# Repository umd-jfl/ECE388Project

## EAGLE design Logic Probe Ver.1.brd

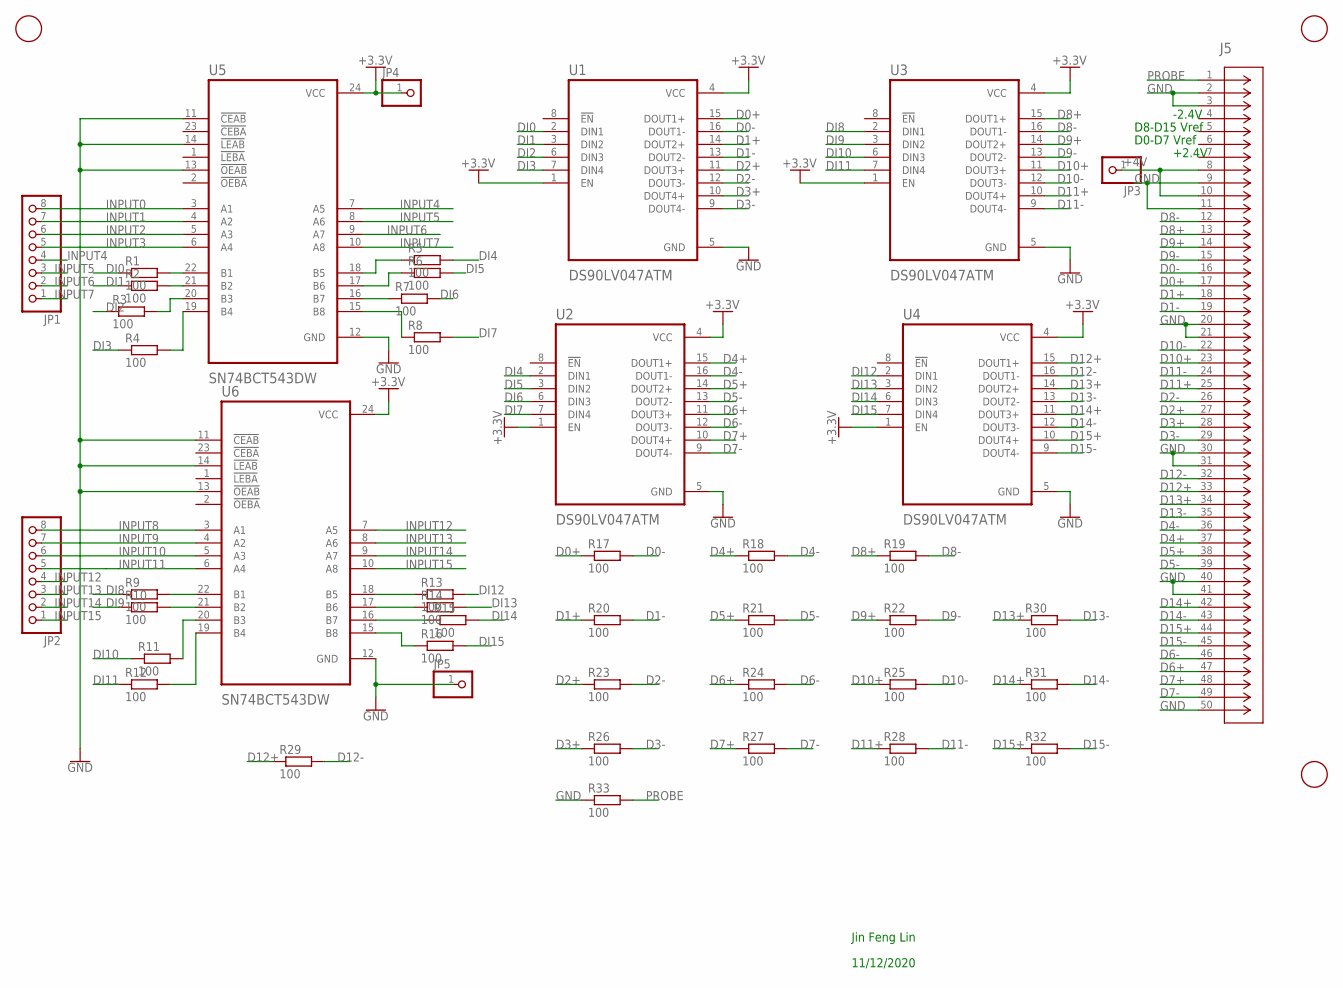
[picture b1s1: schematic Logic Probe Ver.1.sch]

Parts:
J5: TST-125-01-G-D; CONN_TST-125-XX-X-D_SAI
JP1, JP2: PINHD-1X8LOCK; 1X08-LOCK
JP3, JP4, JP5: PINHD-1X1; 1X01
R1, R2, R3, R4, R5, R6, R7, R8, R9, R10, R11, R12, R13, R14, R15, R16, R17, R18, R19, R20, R21, R22, R23, R24, R25, R26, R27, R28, R29, R30, R31, R32, R33: 100; R0805
U1, U2, U3, U4: DS90LV047ATM; SOIC127P600X175-16N
U5, U6: SN74BCT543DW; SOIC127P1030X265-24N
U$1, U$2, U$3: FIDUCIAL; FIDUCIAL_1MM

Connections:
+3.3V: JP4.1, U1.1 (EN), U1.4 (VCC), U2.1 (EN), U2.4 (VCC), U3.1 (EN), U3.4 (VCC), U4.1 (EN), U4.4 (VCC), U5.24 (VCC), U6.24 (VCC)
+4V: J5.8, J5.10, JP3.1
D0+: J5.17, R17.1, U1.15 (DOUT1+)
D0-: J5.16, R17.2, U1.16 (DOUT1-)
D1+: J5.18, R20.1, U1.14 (DOUT2+)
D1-: J5.19, R20.2, U1.13 (DOUT2-)
D2+: J5.27, R23.1, U1.11 (DOUT3+)
D2-: J5.26, R23.2, U1.12 (DOUT3-)
D3+: J5.28, R26.1, U1.10 (DOUT4+)
D3-: J5.29, R26.2, U1.9 (DOUT4-)
D4+: J5.37, R18.1, U2.15 (DOUT1+)
D4-: J5.36, R18.2, U2.16 (DOUT1-)
D5+: J5.38, R21.1, U2.14 (DOUT2+)
D5-: J5.39, R21.2, U2.13 (DOUT2-)
D6+: J5.47, R24.1, U2.11 (DOUT3+)
D6-: J5.46, R24.2, U2.12 (DOUT3-)
D7+: J5.48, R27.1, U2.10 (DOUT4+)
D7-: J5.49, R27.2, U2.9 (DOUT4-)
D8+: J5.13, R19.1, U3.15 (DOUT1+)
D8-: J5.12, R19.2, U3.16 (DOUT1-)
D9+: J5.14, R22.1, U3.14 (DOUT2+)
D9-: J5.15, R22.2, U3.13 (DOUT2-)
D10+: J5.23, R25.1, U3.11 (DOUT3+)
D10-: J5.22, R25.2, U3.12 (DOUT3-)
D11+: J5.25, R28.1, U3.10 (DOUT4+)
D11-: J5.24, R28.2, U3.9 (DOUT4-)
D12+: J5.33, R29.1, U4.15 (DOUT1+)
D12-: J5.32, R29.2, U4.16 (DOUT1-)
D13+: J5.34, R30.1, U4.14 (DOUT2+)
D13-: J5.35, R30.2, U4.13 (DOUT2-)
D14+: J5.42, R31.1, U4.11 (DOUT3+)
D14-: J5.43, R31.2, U4.12 (DOUT3-)
D15+: J5.44, R32.1, U4.10 (DOUT4+)
D15-: J5.45, R32.2, U4.9 (DOUT4-)
DI0: R1.1, U1.2 (DIN1)
DI1: R2.1, U1.3 (DIN2)
DI2: R3.1, U1.6 (DIN3)
DI3: R4.1, U1.7 (DIN4)
DI4: R5.2, U2.2 (DIN1)
DI5: R6.2, U2.3 (DIN2)
DI6: R7.2, U2.6 (DIN3)
DI7: R8.2, U2.7 (DIN4)
DI8: R9.1, U3.2 (DIN1)
DI9: R10.1, U3.3 (DIN2)
DI10: R11.1, U3.6 (DIN3)
DI11: R12.1, U3.7 (DIN4)
DI12: R13.2, U4.2 (DIN1)
DI13: R14.2, U4.3 (DIN2)
DI14: R15.2, U4.6 (DIN3)
DI15: R16.2, U4.7 (DIN4)
GND: J5.2, J5.3, J5.9, J5.11, J5.20, J5.21, J5.30, J5.31, J5.40, J5.41, J5.50, JP5.1, R33.1, U1.5 (GND), U2.5 (GND), U3.5 (GND), U4.5 (GND), U5.11 (!CEAB), U5.12 (GND), U5.13 (!OEAB), U5.14 (!LEAB), U6.11 (!CEAB), U6.12 (GND), U6.13 (!OEAB), U6.14 (!LEAB)
INPUT0: JP1.8, U5.3 (A1)
INPUT1: JP1.7, U5.4 (A2)
INPUT2: JP1.6, U5.5 (A3)
INPUT3: JP1.5, U5.6 (A4)
INPUT4: JP1.4, U5.7 (A5)
INPUT5: JP1.3, U5.8 (A6)
INPUT6: JP1.2, U5.9 (A7)
INPUT7: JP1.1, U5.10 (A8)
INPUT8: JP2.8, U6.3 (A1)
INPUT9: JP2.7, U6.4 (A2)
INPUT10: JP2.6, U6.5 (A3)
INPUT11: JP2.5, U6.6 (A4)
INPUT12: JP2.4, U6.7 (A5)
INPUT13: JP2.3, U6.8 (A6)
INPUT14: JP2.2, U6.9 (A7)
INPUT15: JP2.1, U6.10 (A8)
unnamed: R12.2, U6.19 (B4)
unnamed: R11.2, U6.20 (B3)
unnamed: R10.2, U6.21 (B2)
unnamed: R9.2, U6.22 (B1)
unnamed: R13.1, U6.18 (B5)
unnamed: R14.1, U6.17 (B6)
unnamed: R15.1, U6.16 (B7)
unnamed: R16.1, U6.15 (B8)
unnamed: R4.2, U5.19 (B4)
unnamed: R3.2, U5.20 (B3)
unnamed: R2.2, U5.21 (B2)
unnamed: R1.2, U5.22 (B1)
unnamed: R5.1, U5.18 (B5)
unnamed: R6.1, U5.17 (B6)
unnamed: R7.1, U5.16 (B7)
unnamed: R8.1, U5.15 (B8)
PROBE: J5.1, R33.2

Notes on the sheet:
-2.4V
D8-D15 Vref
D0-D7 Vref
+2.4V
11/12/2020
Jin Feng Lin

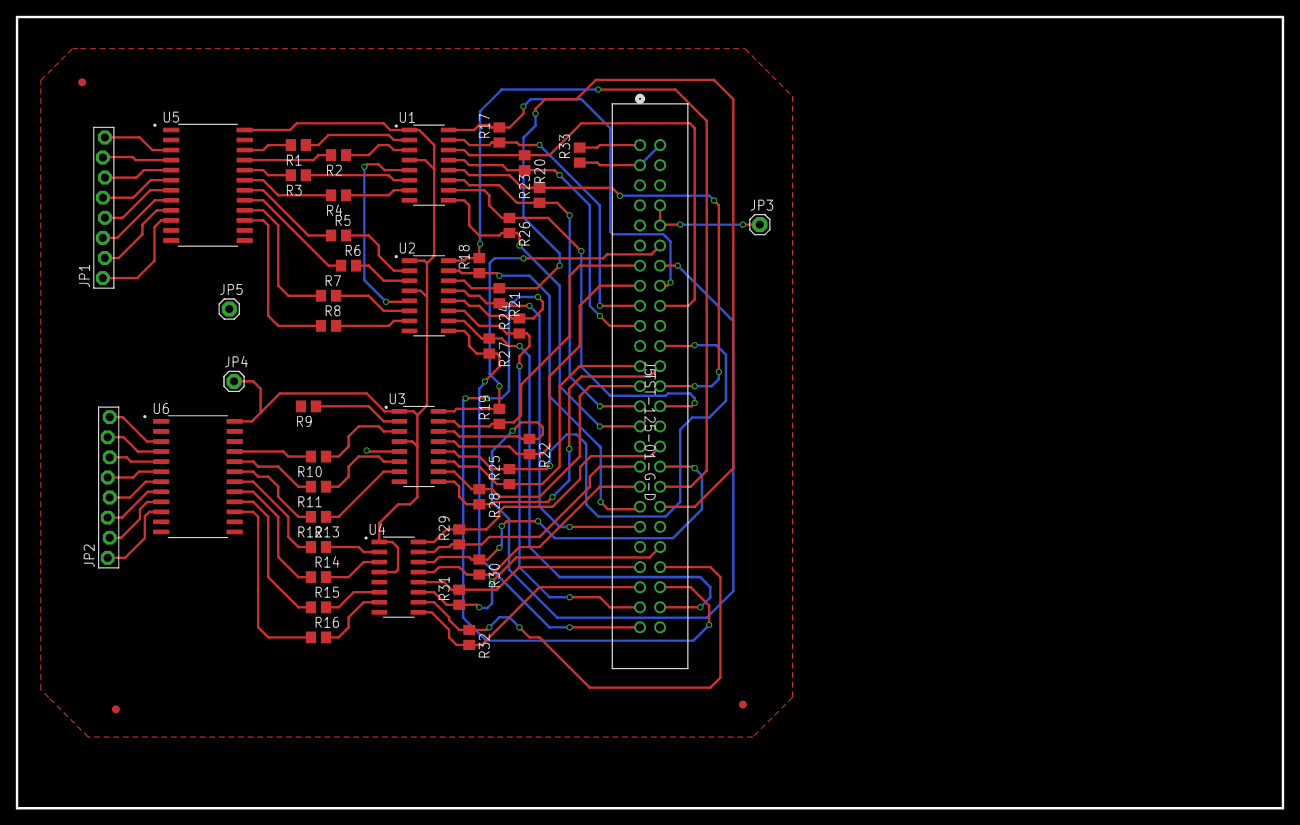
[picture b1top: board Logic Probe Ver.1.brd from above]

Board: 2 copper layers, 160.0 x 100.0 mm, 48 parts (0 on the bottom side), 84 nets.

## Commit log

2020-10-08 Upload the Parts List
    Upload the initial parts list for the chosen project of ECE388: Logic Analyzer Probe
2020-10-17 Updated BOM
    Replace some components are suggested by Tim. Fix the format to be as the given example
2020-11-06 Create logic analyzer probe.pdf
    Initial draft of the logic analyzer probe shematic
2020-11-06 Gerber Submission
    PCB layout base on initial draft of schematic
2020-11-12 Schematic 1.0
    Changed the frame to the desire US Letter frame and published as required
2020-11-12 Update Schematic
    Modify schematic to allow input signals to be send into the board
2020-11-12 PCB Submission 2.0
    Modify the PCB to fulfill the comments received from initial submission. All eagle files are upload as well.
2020-11-12 Double Check on PCB
    Double check that the correct CAM output files are pushed to Github
2020-11-12 PCB Submission
    Attempt to fix the comments received for PCB
2020-11-20 BOM for Assembly
    Create a BOM for board assembled

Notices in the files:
parts and their libraries:
COPYRIGHT: Copyright (C) 2018 Accelerated Designs. All rights reserved
SparkFun-PowerSymbols: Licensing: Creative Commons ShareAlike 4.0 International - https://creativecommons.org/licenses/by-sa/4.0
